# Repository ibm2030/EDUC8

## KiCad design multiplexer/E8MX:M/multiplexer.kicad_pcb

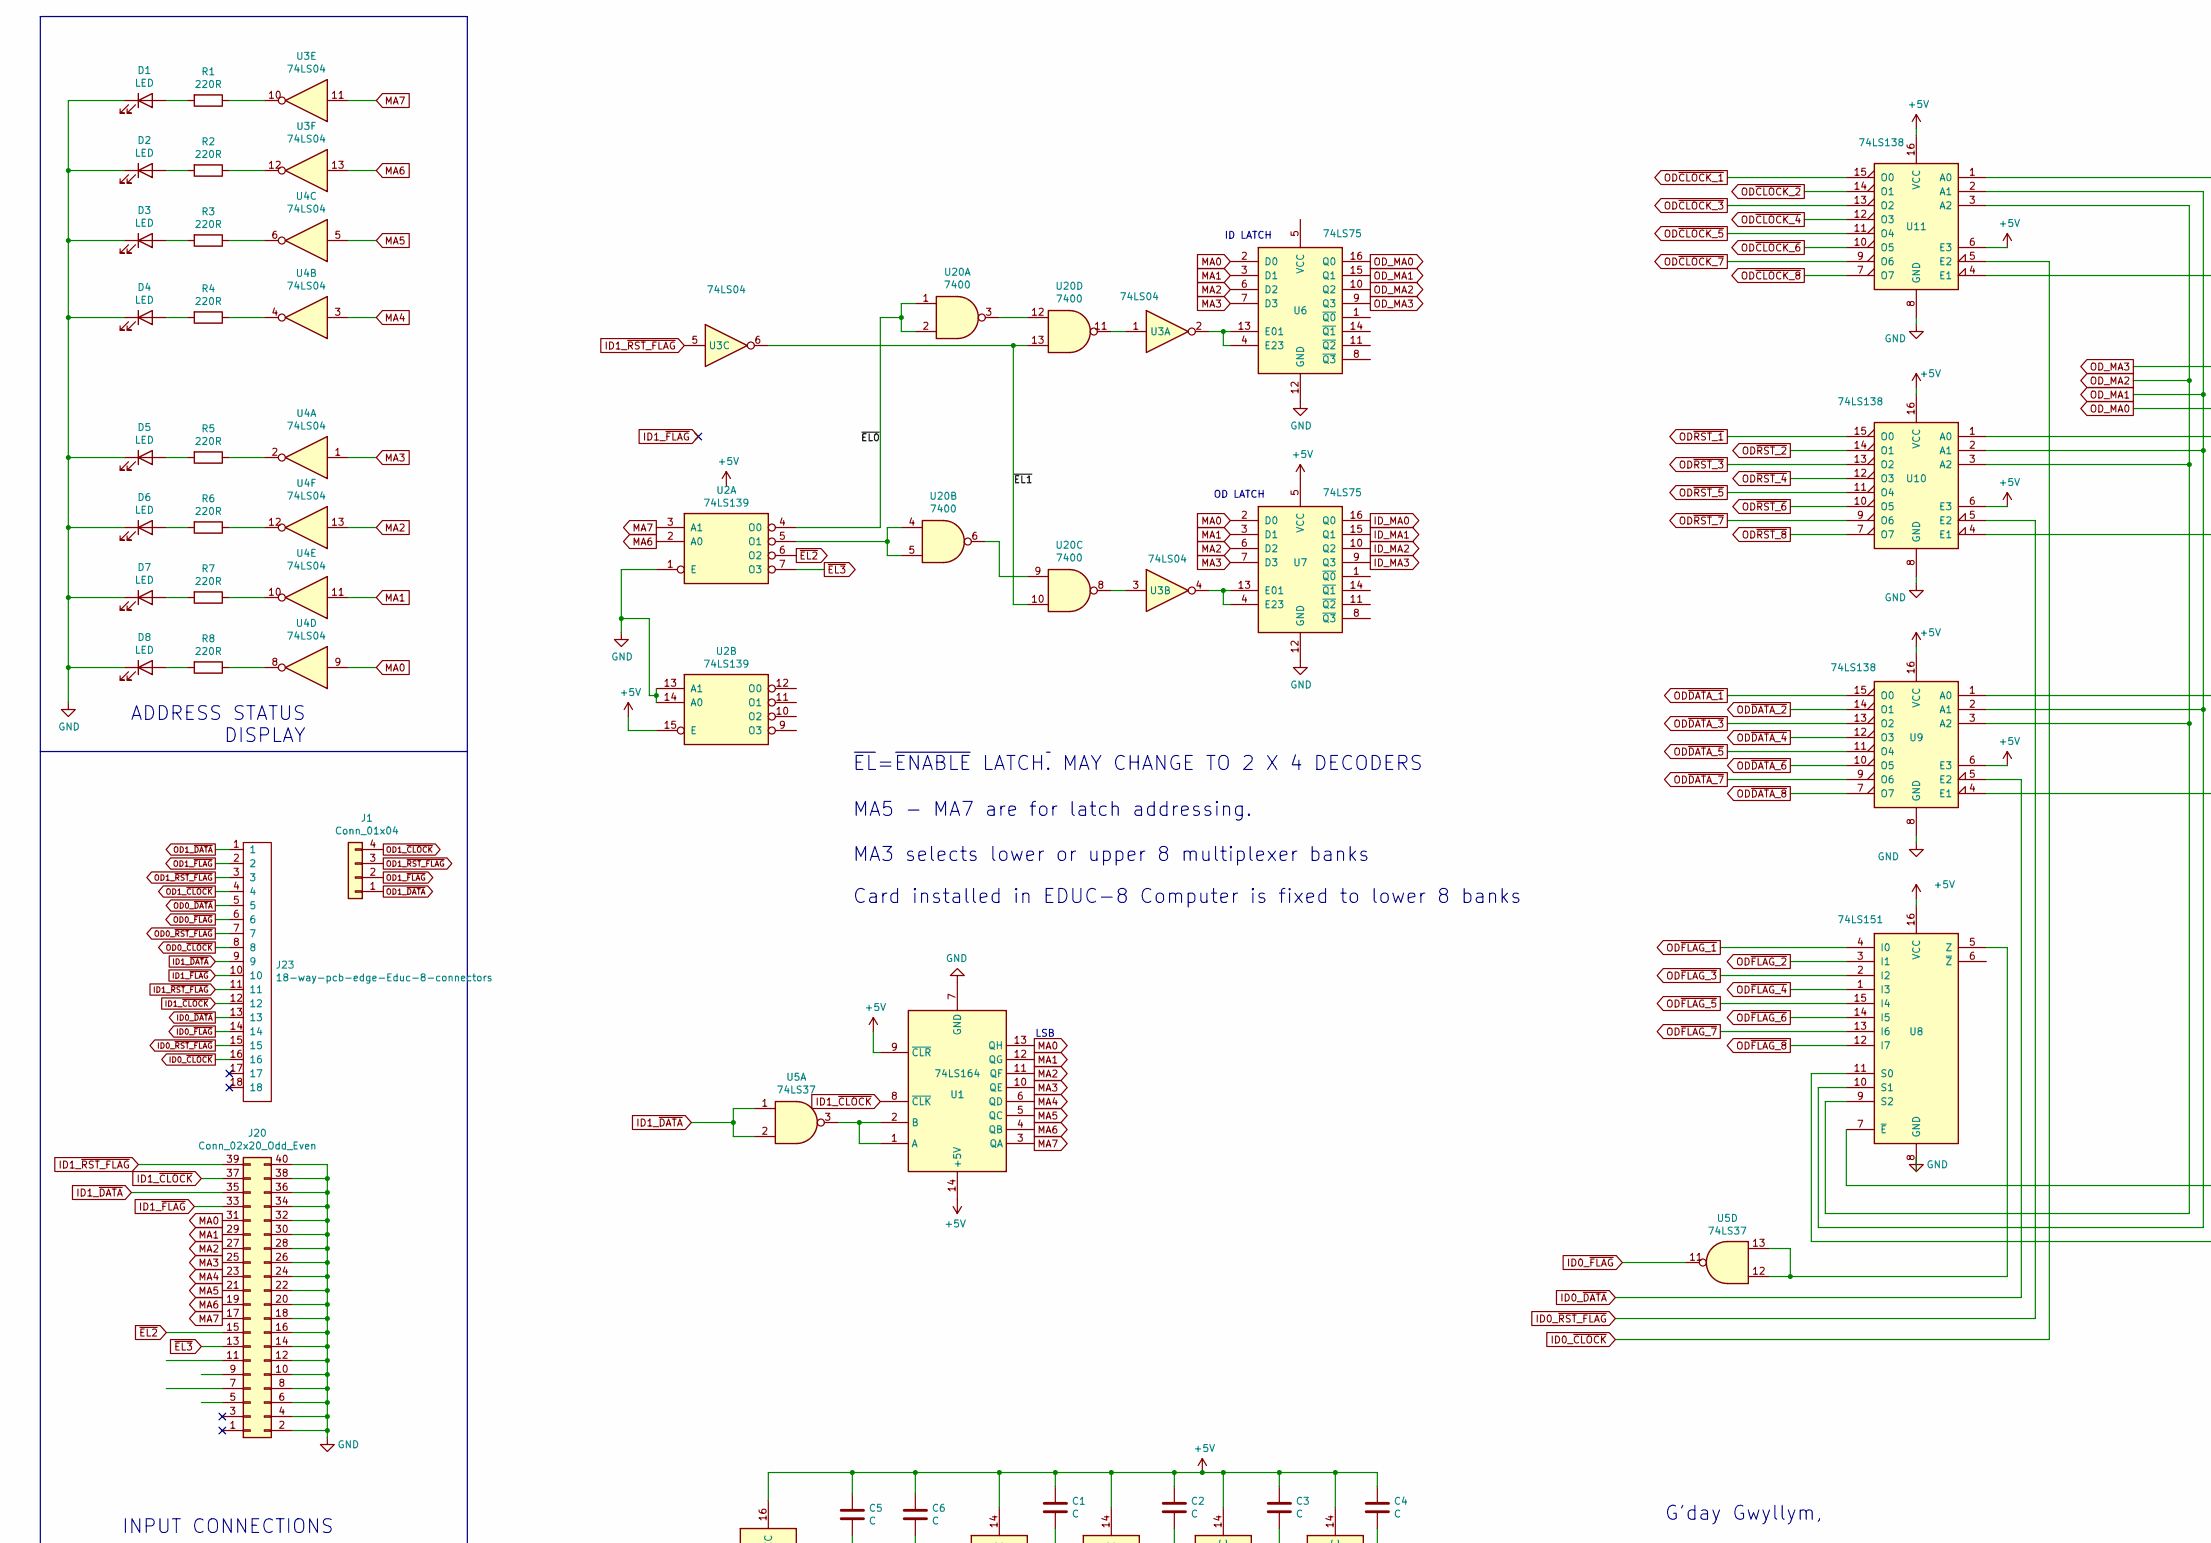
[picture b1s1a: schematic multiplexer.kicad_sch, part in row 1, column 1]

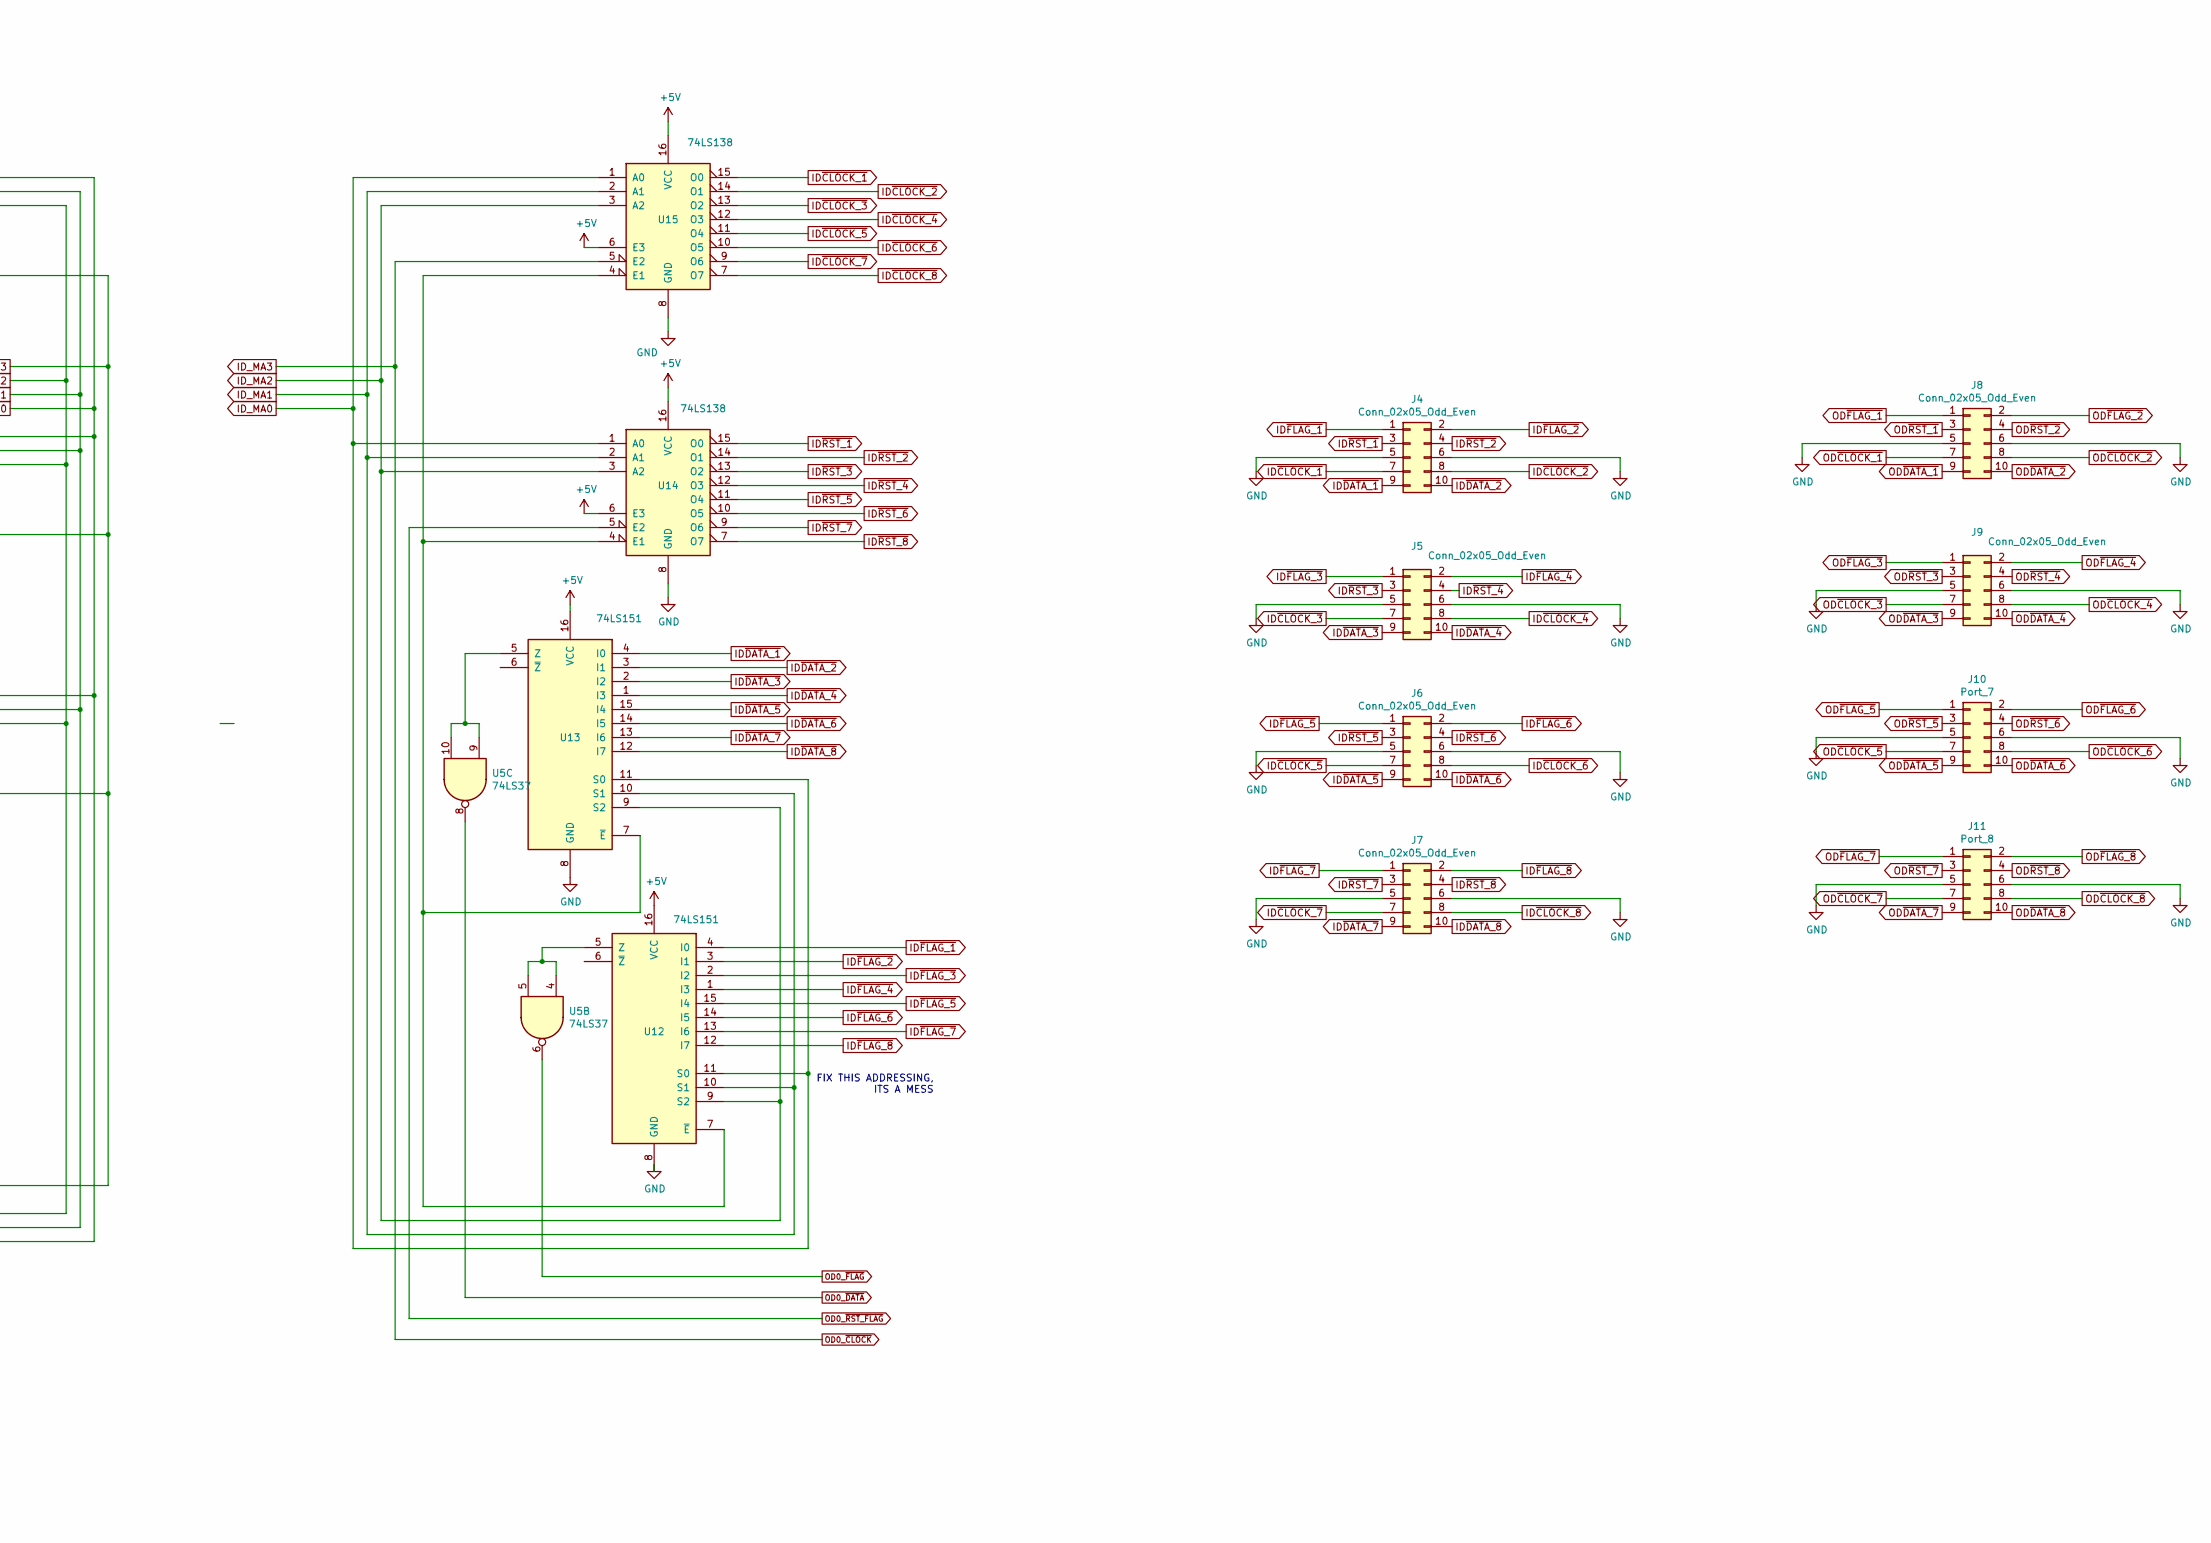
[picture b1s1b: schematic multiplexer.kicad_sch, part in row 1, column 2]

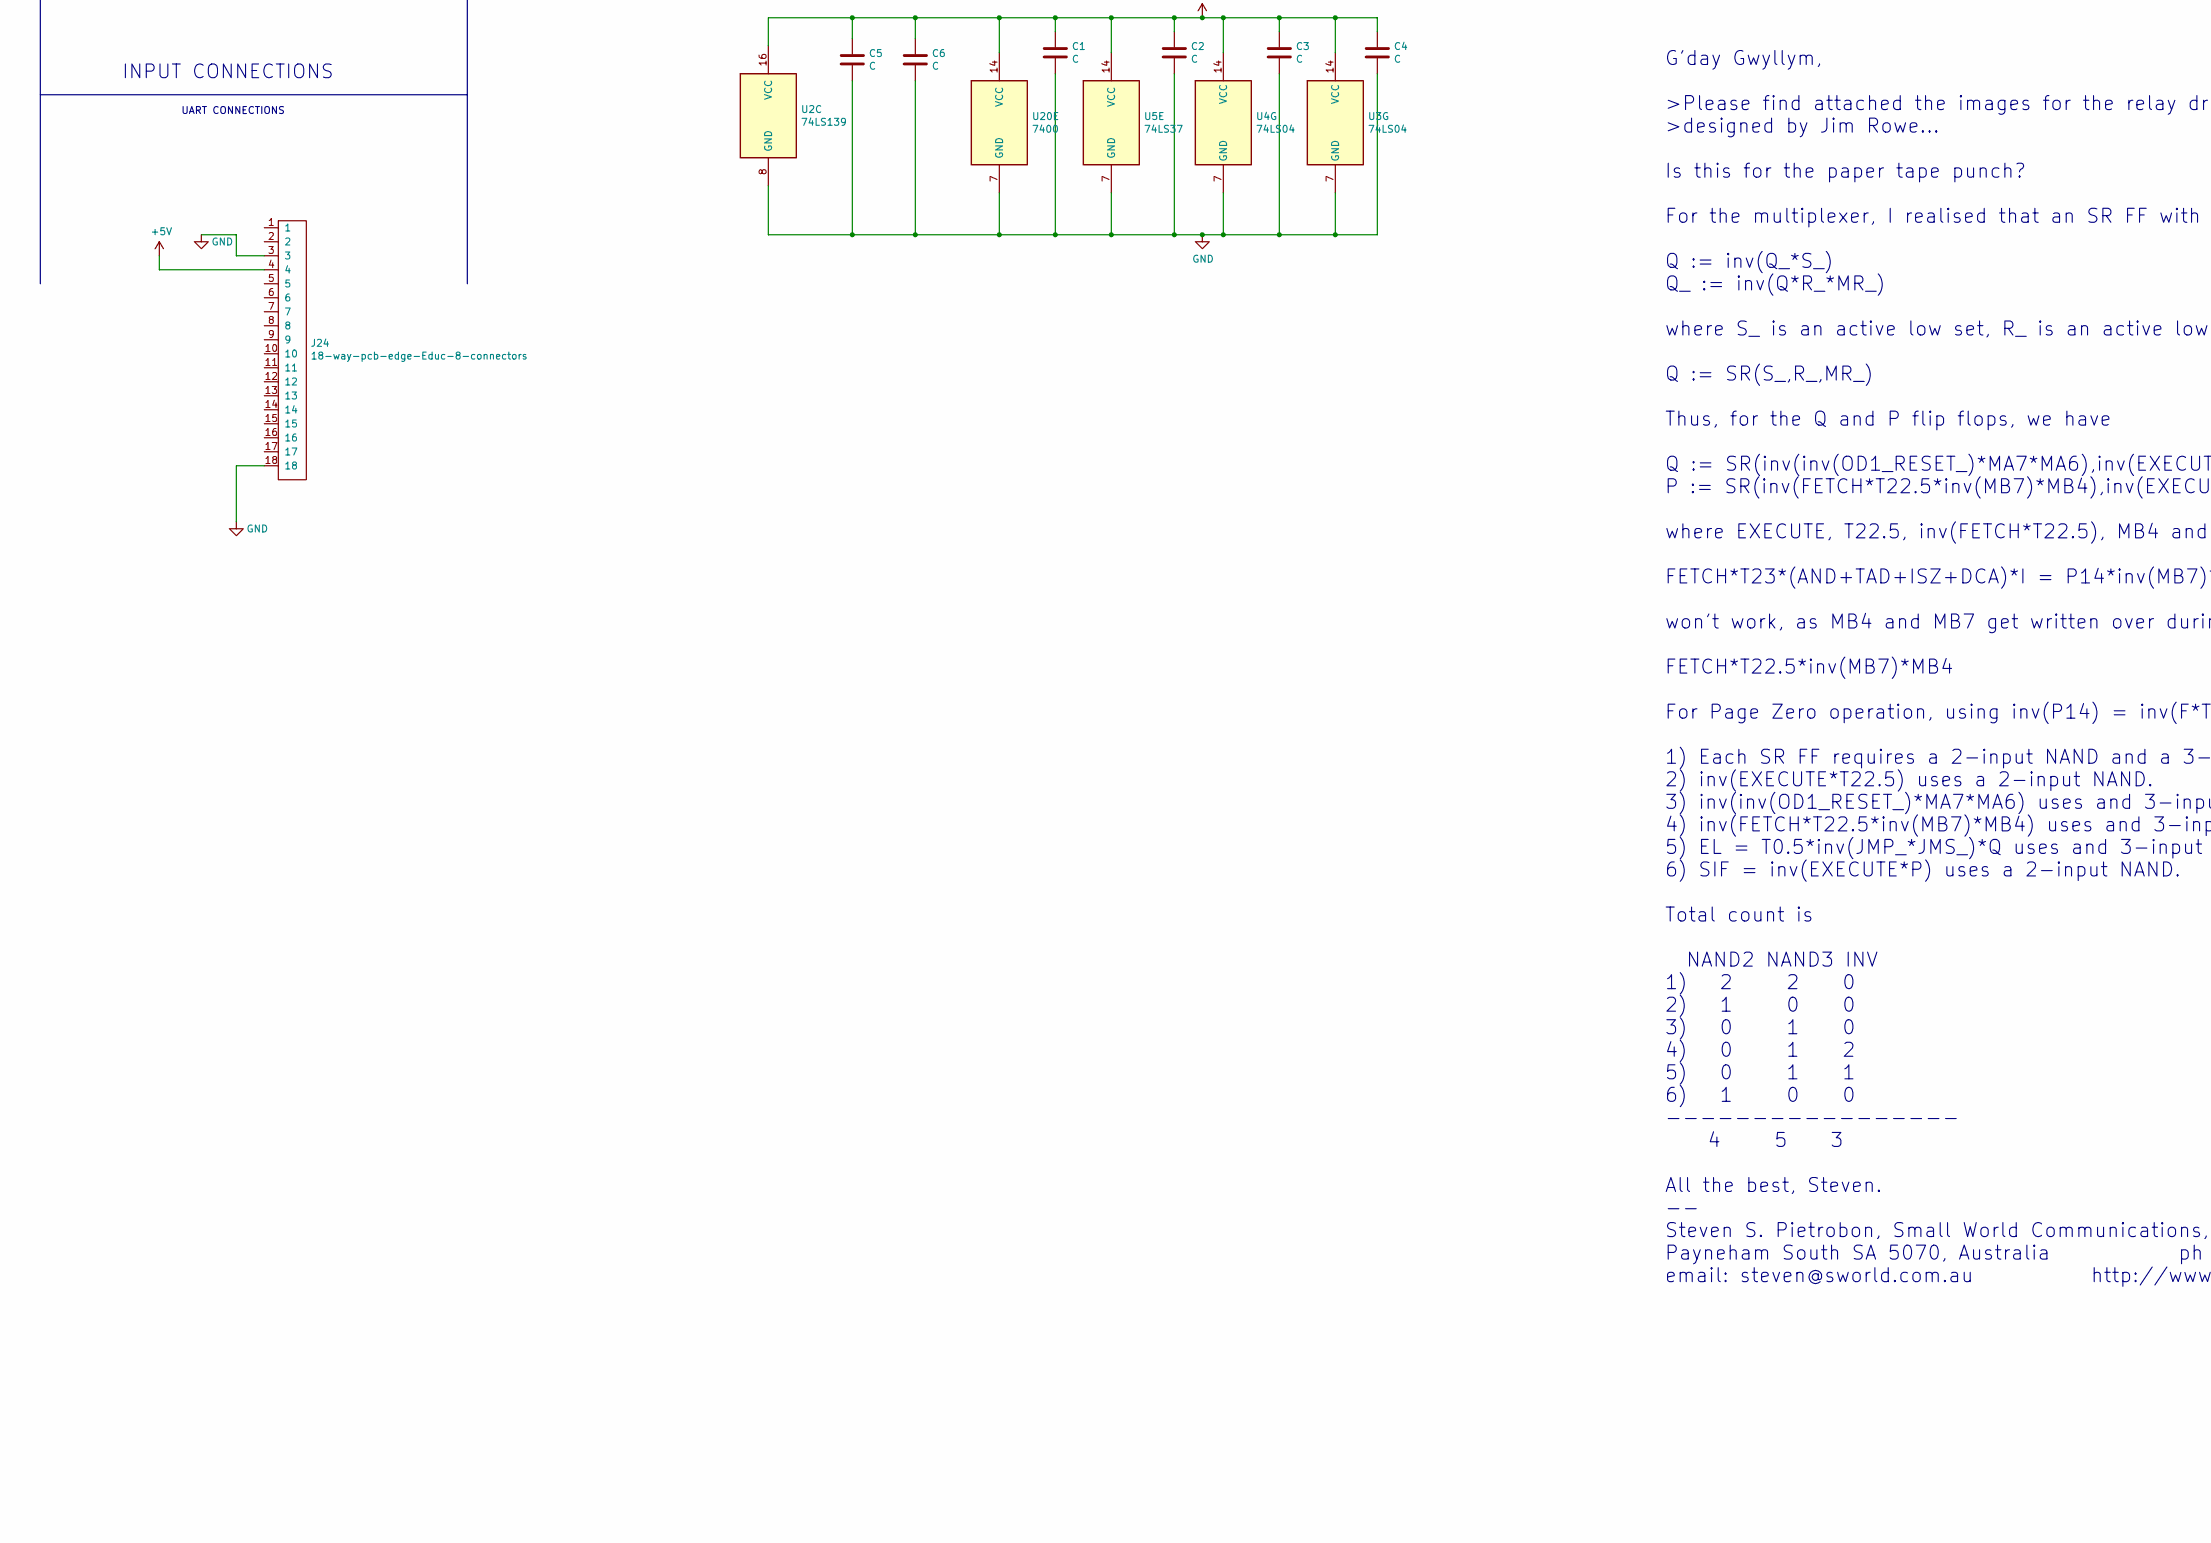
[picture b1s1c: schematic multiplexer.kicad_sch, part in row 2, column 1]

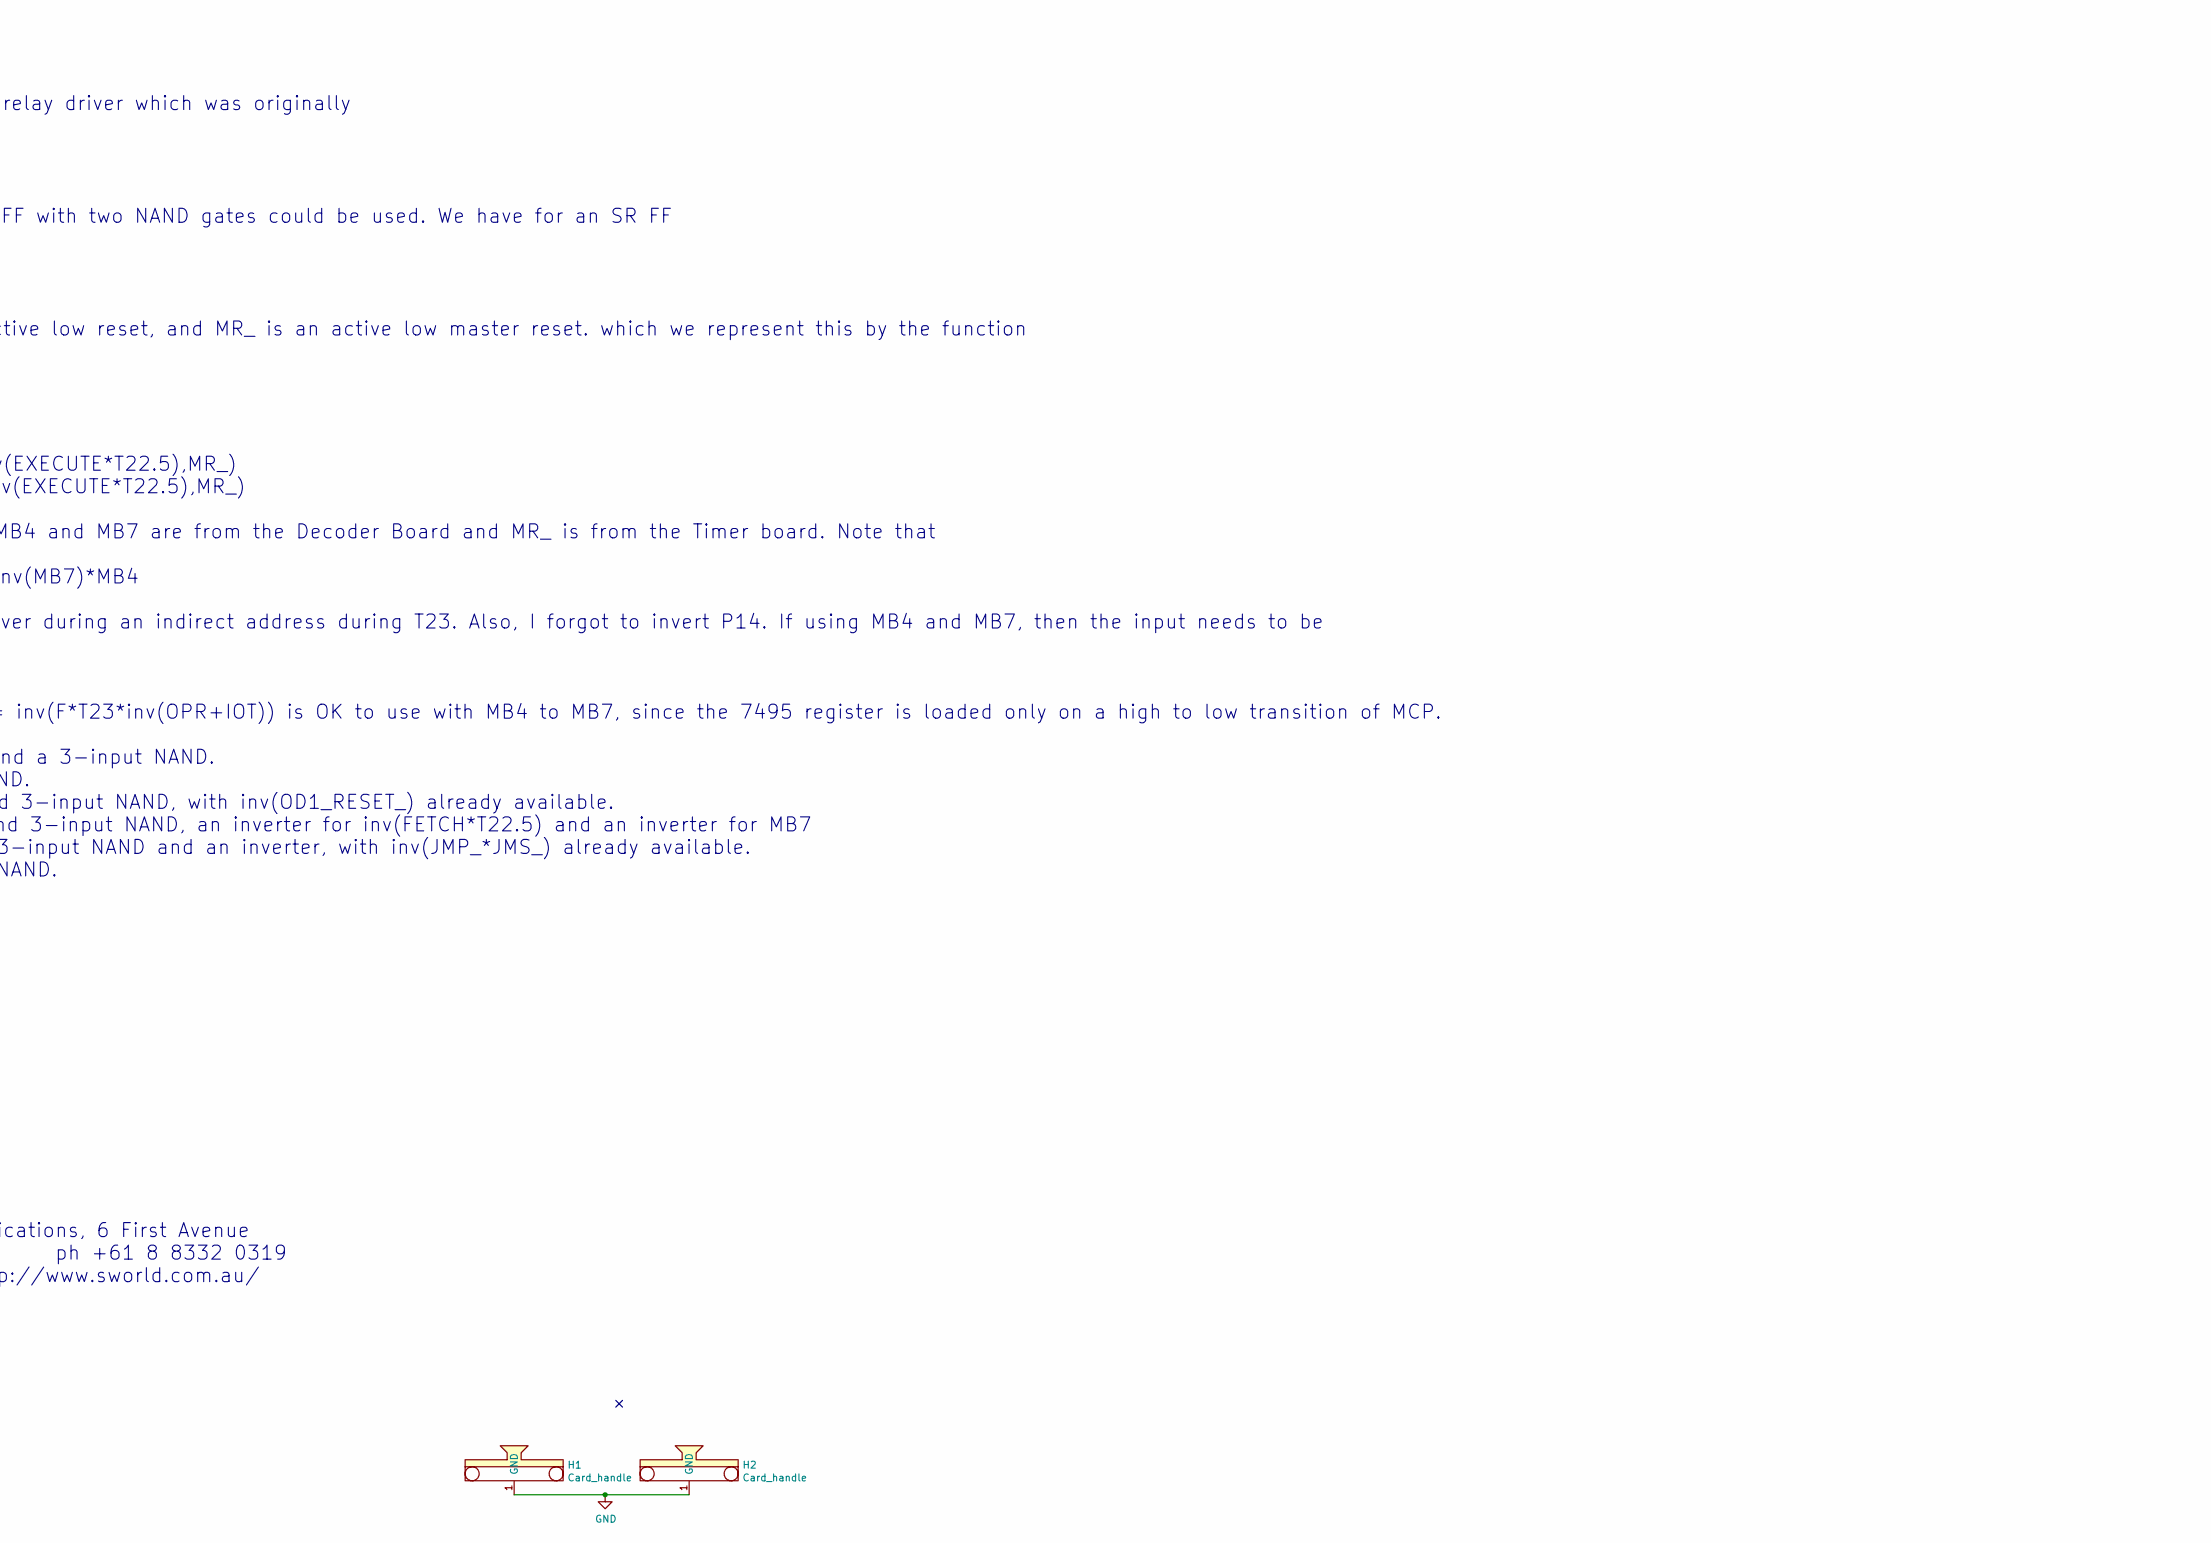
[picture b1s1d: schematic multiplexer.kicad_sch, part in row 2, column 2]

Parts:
C1, C2, C3, C4, C5, C6: C; C_Rect_L7.2mm_W2.5mm_P5.00mm_FKS2_FKP2_MKS2_MKP2
D1, D2, D3, D4, D5, D6, D7, D8: LED; LED_D5.0mm
H1, H2: Card_handle
J1: Conn_01x04; PinHeader_1x04_P2.54mm_Vertical
J4, J5, J6, J7, J8, J9: Conn_02x05_Odd_Even; IDC-Header_2x05_P2.54mm_Vertical
J10: Port_7; IDC-Header_2x05_P2.54mm_Vertical
J11: Port_8; IDC-Header_2x05_P2.54mm_Vertical
J20: Conn_02x20_Odd_Even; IDC-Header_2x20_P2.54mm_Horizontal
J23, J24: 18-way-pcb-edge-Educ-8-connectors; PCB_18pin
R1, R2, R3, R4, R5, R6, R7, R8: 220R; R_Axial_DIN0207_L6.3mm_D2.5mm_P15.24mm_Horizontal
U1: 74LS164; DIP-14_W7.62mm
U2: 74LS139; DIP-16_W7.62mm
U3: 74LS04
U4: 74LS04; DIP-14_W7.62mm_LongPads
U5: 74LS37; DIP-14_W7.62mm
U6, U7: 74LS75; DIP-16_W7.62mm
U8, U12, U13: 74LS151; DIP-16_W7.62mm
U9: 74LS138; DIP-16_W7.62mm_LongPads
U10, U11, U14, U15: 74LS138; DIP-16_W7.62mm
U20: 7400

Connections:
+5V: C1.1, C2.1, C3.1, C4.1, C5.1, C6.1, J24.4, U1.9 (~CLR), U1.14 (+5V), U2.15 (E), U2.16 (VCC), U3.14 (VCC), U4.14 (VCC), U5.14 (VCC), U7.5 (VCC), U8.16 (VCC), U9.6 (E3), U9.16 (VCC), U10.6 (E3), U10.16 (VCC), U11.6 (E3), U11.16 (VCC), U12.16 (VCC), U13.16 (VCC), U14.6 (E3), U14.16 (VCC), U15.6 (E3), U15.16 (VCC), U20.14 (VCC)
/~EL1: U3.6, U20.10, U20.13
ID0_~CLOCK: J23.16, U11.5 (E2)
ID0_~DATA: J23.13, U9.5 (E2)
ID0_~FLAG: J23.14, U5.11
ID0_~RST_FLAG: J23.15, U10.5 (E2)
ID1_~CLOCK: J20.37, J23.12, U1.8 (~CLK)
ID1_~DATA: J20.35, J23.9, U5.1, U5.2
ID1_~FLAG: J20.33, J23.10
ID1_~RST_FLAG: J20.39, J23.11, U3.5
ID_MA0: U7.16 (Q0), U12.11 (S0), U13.11 (S0), U14.1 (A0), U15.1 (A0)
ID_MA1: U7.15 (Q1), U12.10 (S1), U13.10 (S1), U14.2 (A1), U15.2 (A1)
ID_MA2: U7.10 (Q2), U12.9 (S2), U13.9 (S2), U14.3 (A2), U15.3 (A2)
ID_MA3: J23.8, U7.9 (Q3), U15.5 (E2)
ID~CLOCK_1: J4.7, U15.15 (O0)
ID~CLOCK_2: J4.8, U15.14 (O1)
ID~CLOCK_3: J5.7, U15.13 (O2)
ID~CLOCK_4: J5.8, U15.12 (O3)
ID~CLOCK_5: J6.7, U15.11 (O4)
ID~CLOCK_6: J6.8, U15.10 (O5)
ID~CLOCK_7: J7.7, U15.9 (O6)
ID~CLOCK_8: J7.8, U15.7 (O7)
ID~DATA_1: J4.9, U13.4 (I0)
ID~DATA_2: J4.10, U13.3 (I1)
ID~DATA_3: J5.9, U13.2 (I2)
ID~DATA_4: J5.10, U13.1 (I3)
ID~DATA_5: J6.9, U13.15 (I4)
ID~DATA_6: J6.10, U13.14 (I5)
ID~DATA_7: J7.9, U13.13 (I6)
ID~DATA_8: J7.10, U13.12 (I7)
ID~FLAG_1: J4.1, U12.4 (I0)
ID~FLAG_2: J4.2, U12.3 (I1)
ID~FLAG_3: J5.1, U12.2 (I2)
ID~FLAG_4: J5.2, U12.1 (I3)
ID~FLAG_5: J6.1, U12.15 (I4)
ID~FLAG_6: J6.2, U12.14 (I5)
ID~FLAG_7: J7.1, U12.13 (I6)
ID~FLAG_8: J7.2, U12.12 (I7)
ID~RST_1: J4.3, U14.15 (O0)
ID~RST_2: J4.4, U14.14 (O1)
ID~RST_3: J5.3, U14.13 (O2)
ID~RST_4: J5.4, U14.12 (O3)
ID~RST_5: J6.3, U14.11 (O4)
ID~RST_6: J6.4, U14.10 (O5)
ID~RST_7: J7.3, U14.9 (O6)
ID~RST_8: J7.4, U14.7 (O7)
MA0: J20.31, U1.13 (QH), U4.9, U6.2 (D0), U7.2 (D0)
MA1: J20.29, U1.12 (QG), U4.11, U6.3 (D1), U7.3 (D1)
MA2: J20.27, U1.11 (QF), U4.13, U6.6 (D2), U7.6 (D2)
MA3: J20.25, U1.10 (QE), U4.1, U6.7 (D3), U7.7 (D3)
MA4: J20.23, U1.6 (QD), U4.3
MA5: J20.21, U1.5 (QC), U4.5
MA6: J20.19, U1.4 (QB), U2.2 (A0), U3.13
MA7: J20.17, U1.3 (QA), U2.3 (A1), U3.11
unnamed: D1.2 (A), R1.2
unnamed: D2.2 (A), R2.2
unnamed: D3.2 (A), R3.2
unnamed: D4.2 (A), R4.2
unnamed: D5.2 (A), R5.2
unnamed: D6.2 (A), R6.2
unnamed: D7.2 (A), R7.2
unnamed: D8.2 (A), R8.2
unnamed: R1.1, U3.10
unnamed: R2.1, U3.12
unnamed: R3.1, U4.6
unnamed: R4.1, U4.4
unnamed: R5.1, U4.2
unnamed: R6.1, U4.12
unnamed: R7.1, U4.10
unnamed: R8.1, U4.8
unnamed: U1.1 (A), U1.2 (B), U5.3
unnamed: U2.4 (O0), U20.1, U20.2
unnamed: U2.5 (O1), U20.4, U20.5
unnamed: U3.2, U6.4 (E23), U6.13 (E01)
unnamed: U3.4, U7.4 (E23), U7.13 (E01)
unnamed: U5.12, U5.13, U8.5 (Z)
unnamed: U5.4, U5.5, U12.5 (Z)
unnamed: U12.7 (~E), U13.7 (~E), U14.4 (E1), U15.4 (E1)
unnamed: U5.9, U5.10, U13.5 (Z)
unnamed: U20.6, U20.9
unnamed: U3.3, U20.8
unnamed: U3.1, U20.11
unnamed: U20.3, U20.12
OD0_~DATA: J23.5, U5.8
OD0_~FLAG: J23.6, U5.6
OD0_~RST_FLAG: J23.7, U14.5 (E2)
OD1_~CLOCK: J1.4, J23.4
OD1_~DATA: J1.1, J23.1
OD1_~FLAG: J1.2, J23.2
OD1_~RST_FLAG: J1.3, J23.3
OD_MA0: U6.16 (Q0), U8.11 (S0), U9.1 (A0), U10.1 (A0), U11.1 (A0)
OD_MA1: U6.15 (Q1), U8.10 (S1), U9.2 (A1), U10.2 (A1), U11.2 (A1)
OD_MA2: U6.10 (Q2), U8.9 (S2), U9.3 (A2), U10.3 (A2), U11.3 (A2)
OD_MA3: U6.9 (Q3), U8.7 (~E), U9.4 (E1), U10.4 (E1), U11.4 (E1)
OD~CLOCK_1: J8.7, U11.15 (O0)
OD~CLOCK_2: J8.8, U11.14 (O1)
OD~CLOCK_3: J9.7, U11.13 (O2)
OD~CLOCK_4: J9.8, U11.12 (O3)
OD~CLOCK_5: J10.7, U11.11 (O4)
OD~CLOCK_6: J10.8, U11.10 (O5)
OD~CLOCK_7: J11.7, U11.9 (O6)
OD~CLOCK_8: J11.8, U11.7 (O7)
OD~DATA_1: J8.9, U9.15 (O0)
OD~DATA_2: J8.10, U9.14 (O1)
OD~DATA_3: J9.9, U9.13 (O2)
OD~DATA_4: J9.10, U9.12 (O3)
OD~DATA_5: J10.9, U9.11 (O4)
OD~DATA_6: J10.10, U9.10 (O5)
OD~DATA_7: J11.9, U9.9 (O6)
OD~DATA_8: J11.10, U9.7 (O7)
OD~FLAG_1: J8.1, U8.4 (I0)
OD~FLAG_2: J8.2, U8.3 (I1)
OD~FLAG_3: J9.1, U8.2 (I2)
OD~FLAG_4: J9.2, U8.1 (I3)
OD~FLAG_5: J10.1, U8.15 (I4)
OD~FLAG_6: J10.2, U8.14 (I5)
OD~FLAG_7: J11.1, U8.13 (I6)
OD~FLAG_8: J11.2, U8.12 (I7)
OD~RST_1: J8.3, U10.15 (O0)
OD~RST_2: J8.4, U10.14 (O1)
OD~RST_3: J9.3, U10.13 (O2)
OD~RST_4: J9.4, U10.12 (O3)
OD~RST_5: J10.3, U10.11 (O4)
OD~RST_6: J10.4, U10.10 (O5)
OD~RST_7: J11.3, U10.9 (O6)
OD~RST_8: J11.4, U10.7 (O7)
~EL2: J20.15, U2.6 (O2)
~EL3: J20.13, U2.7 (O3)

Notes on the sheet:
Card installed in EDUC-8 Computer is fixed to lower 8 banks
MA5 - MA7 are for latch addressing. MA3 selects lower or upper 8 multiplexer banks
G'day Gwyllym, >Please find attached the images for the relay driver which was originally >designed by Jim Rowe... Is this for the paper tape punch? For the multiplexer, I realised that an SR FF with two NAND gates could be used. We have for an SR FF Q := inv(Q_*S_) Q_ := inv(Q*R_*MR_) where S_ is 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
FIX THIS ADDRESSING, ITS A MESS
ID LATCH
OD LATCH
LSB
UART CONNECTIONS
~{EL}=~{ENABLE} LATCH~{.} MAY CHANGE TO 2 X 4 DECODERS
ADDRESS STATUS DISPLAY
INPUT CONNECTIONS

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
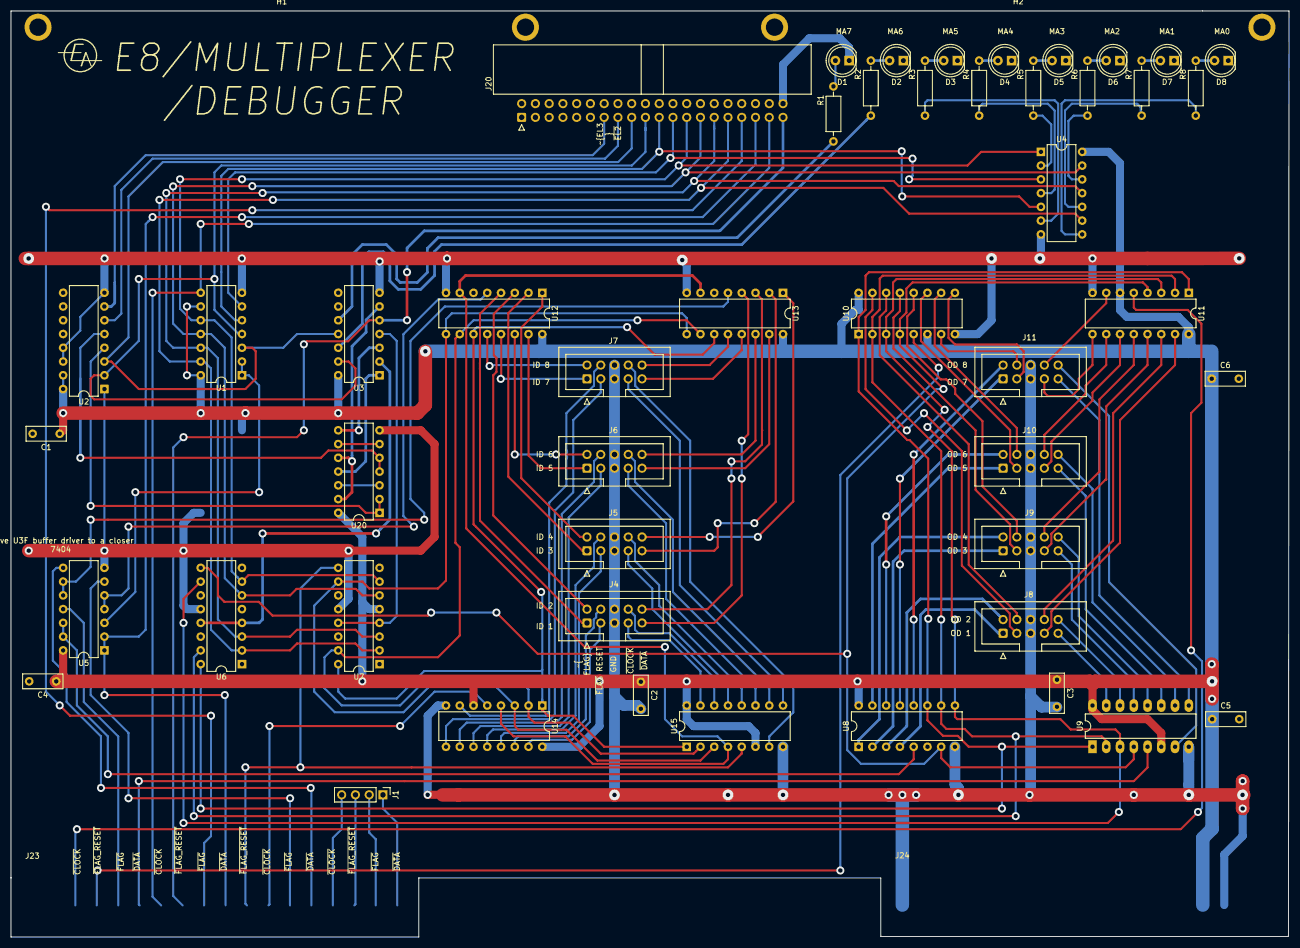
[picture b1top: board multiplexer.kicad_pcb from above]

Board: 2 copper layers, 236.0 x 171.0 mm, 52 parts (0 on the bottom side), 129 nets.

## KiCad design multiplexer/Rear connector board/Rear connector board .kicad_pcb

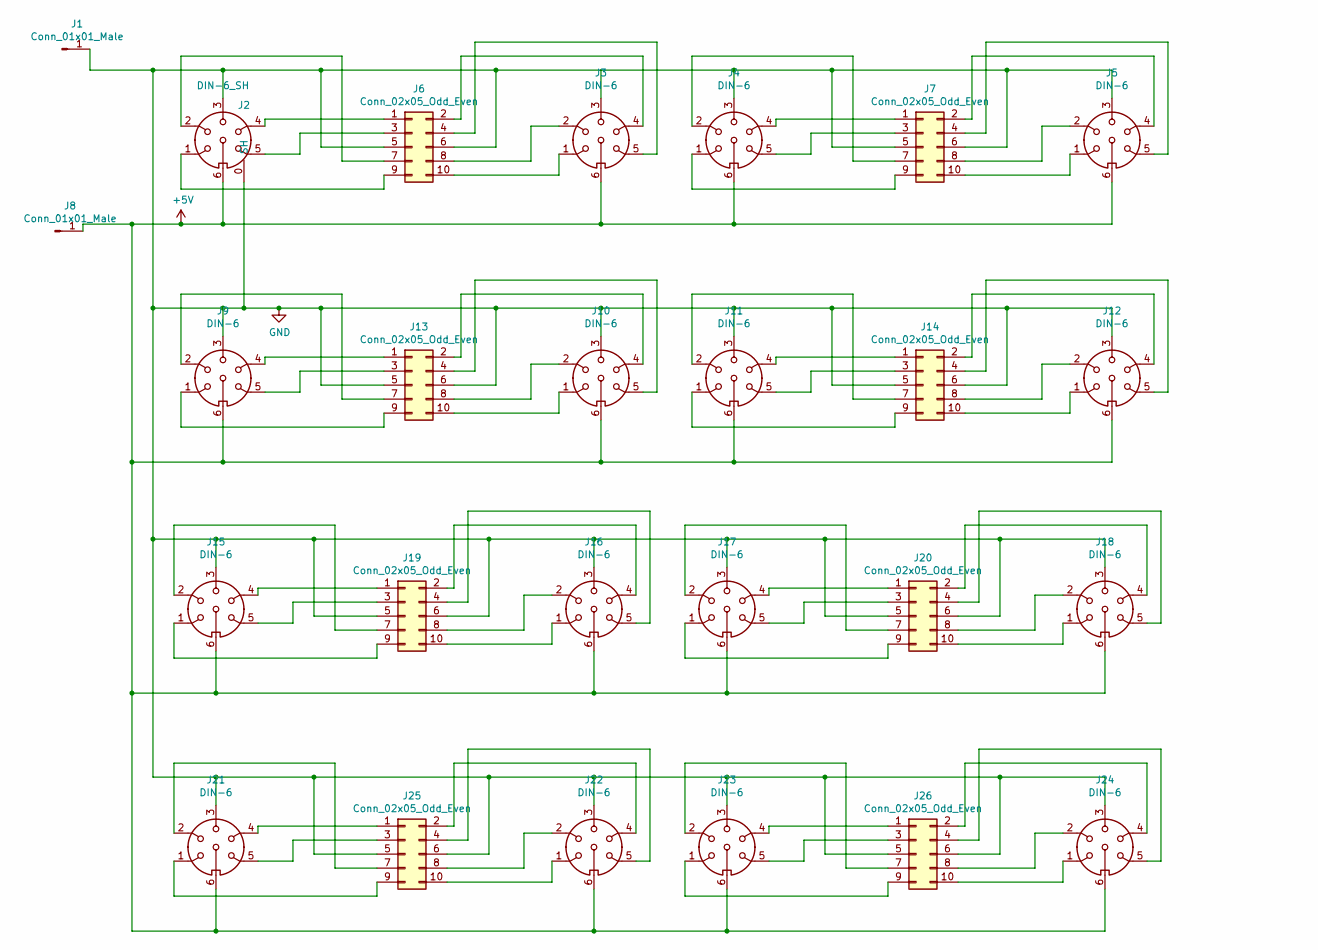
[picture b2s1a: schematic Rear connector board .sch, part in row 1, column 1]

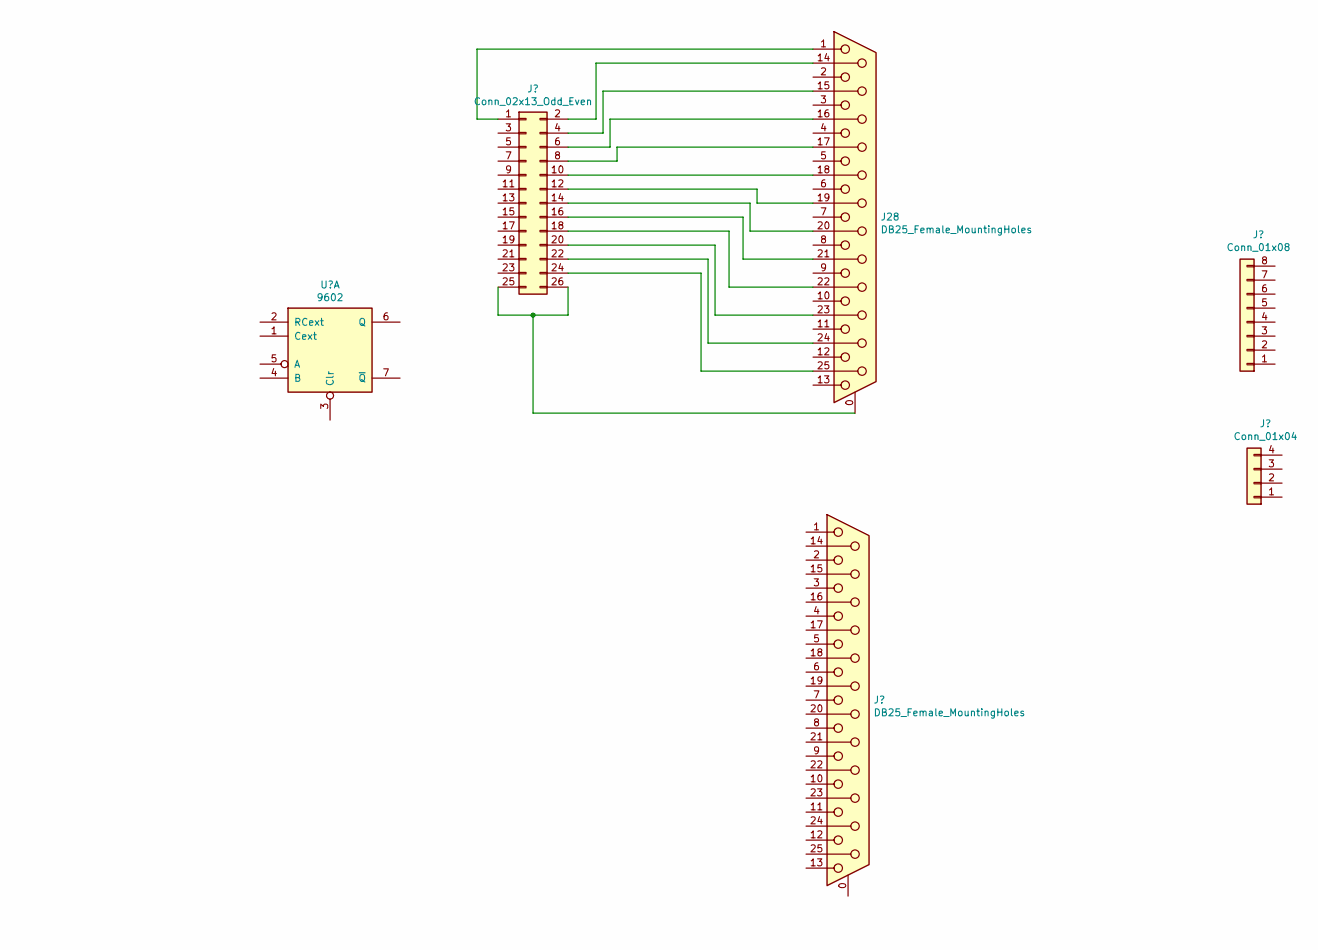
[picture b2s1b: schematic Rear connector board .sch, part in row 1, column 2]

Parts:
J1, J8: Conn_01x01_Male; QC_Terminal_PCB_W6.3mm_P5mm_
J2: DIN-6_SH; 6_PIN_DIN_SOCKET
J3, J4, J5, J9, J10, J11, J12, J15, J16, J17, J18, J21, J22, J23, J24: DIN-6; 6_PIN_DIN_SOCKET
J6, J7, J13, J14, J19, J20, J25, J26: Conn_02x05_Odd_Even; IDC-Header_2x05_P2.54mm_Vertical
J28: DB25_Female_MountingHoles; DSUB-25_Female_Vertical_P2.77x2.84mm_MountingHoles

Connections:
+5V: J2.6, J3.6, J4.6, J5.6, J8.1, J9.6, J10.6, J11.6, J12.6, J15.6, J16.6, J17.6, J18.6, J21.6, J22.6, J23.6, J24.6
GND: J1.1, J2.0 (SH), J2.3, J3.3, J4.3, J5.3, J6.5, J6.6, J7.5, J7.6, J9.3, J10.3, J11.3, J12.3, J13.5, J13.6, J14.5, J14.6, J15.3, J16.3, J17.3, J18.3, J19.5, J19.6, J20.5, J20.6, J21.3, J22.3, J23.3, J24.3, J25.5, J25.6, J26.5, J26.6
unnamed: J2.1, J6.9
unnamed: J2.2, J6.7
unnamed: J2.4, J6.1
unnamed: J2.5, J6.3
unnamed: J3.1, J6.10
unnamed: J3.2, J6.8
unnamed: J3.4, J6.2
unnamed: J3.5, J6.4
unnamed: J4.1, J7.9
unnamed: J4.2, J7.7
unnamed: J4.4, J7.1
unnamed: J4.5, J7.3
unnamed: J5.1, J7.10
unnamed: J5.2, J7.8
unnamed: J5.4, J7.2
unnamed: J5.5, J7.4
unnamed: J10.1, J13.10
unnamed: J10.2, J13.8
unnamed: J10.4, J13.2
unnamed: J10.5, J13.4
unnamed: J11.1, J14.9
unnamed: J11.2, J14.7
unnamed: J11.4, J14.1
unnamed: J11.5, J14.3
unnamed: J12.1, J14.10
unnamed: J12.2, J14.8
unnamed: J12.4, J14.2
unnamed: J12.5, J14.4
unnamed: J9.4, J13.1
unnamed: J9.5, J13.3
unnamed: J9.2, J13.7
unnamed: J9.1, J13.9
unnamed: J15.1, J19.9
unnamed: J15.2, J19.7
unnamed: J15.4, J19.1
unnamed: J15.5, J19.3
unnamed: J16.1, J19.10
unnamed: J16.2, J19.8
unnamed: J16.4, J19.2
unnamed: J16.5, J19.4
unnamed: J17.1, J20.9
unnamed: J17.2, J20.7
unnamed: J17.4, J20.1
unnamed: J17.5, J20.3
unnamed: J18.1, J20.10
unnamed: J18.2, J20.8
unnamed: J18.4, J20.2
unnamed: J18.5, J20.4
unnamed: J21.1, J25.9
unnamed: J21.2, J25.7
unnamed: J21.4, J25.1
unnamed: J21.5, J25.3
unnamed: J22.1, J25.10
unnamed: J22.2, J25.8
unnamed: J22.4, J25.2
unnamed: J22.5, J25.4
unnamed: J23.1, J26.9
unnamed: J23.2, J26.7
unnamed: J23.4, J26.1
unnamed: J23.5, J26.3
unnamed: J24.1, J26.10
unnamed: J24.2, J26.8
unnamed: J24.4, J26.2
unnamed: J24.5, J26.4
